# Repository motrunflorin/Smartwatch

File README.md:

Functionalities:

* Wi-Fi and BLE communication via ESP32
* IMU 6-axis BMI085 for motion sensing
* DRV2605L for haptic feedback
* LiPo battery with MCP73831 charging circuit
* USB-C port for programming and charging
* 1.28-inch LCD display, 240x240 pixels for visual output
* Electronics must fit into the provided case

(All datasheets and schematics are in the Components folder)

Constraints:

* No straight angles in traces.
* Power traces must meet the required dimensions.
* Decoupling capacitors (100nF) should be placed as close as possible to the power pins of modules and ICs.
* For double-sided boards, avoid vias in power traces.
* Main components should be placed according to the mechanical dimension and placement document.
* Power traces (VCC, VUSB, VBUS, 3V3, etc.) should have a width of 0.3mm, and data signals at least 0.125mm.
* The ESP32 antenna should be placed toward the PCB edge, with the PCB cutout beneath it.

Notes and Recommendations:

* Use SMD resistors and capacitors in 0402 package, unless specified otherwise (e.g., 0603, tantalum).
* Component placement should be on the TOP layer (except for test pads, SD card socket, LCD connector, and NOR Flash).
* Routing can be on both top and bottom layers. If using two layers, ensure the ground plane is appropriately designed.
* For DRC checks, load the verification file from the provided archive.
* Apply Via Stitching between the two ground planes, especially near the ESP32 module.
* Ignore "Only INPUT pins on NET ID" error.
* Do not route signals under the ESP32 antenna; the area beneath it must be cut out to minimize interference.
* Errors due to button, header, and USB port placement are disregarded.
* Test pads should be placed only on the back of the PCB, clearly marked in silkscreen with signal names.
* Use the provided library ([hector_watch.zip file]) for component symbols and footprints, except for:
    - Buttons ([button.pdf file])
    - LCD connector (draw your own footprints based on the LCD datasheet).

Files:

* Schematics: Schematics.zip file
* DRC check: DRC_check.zip file
* PCB Dimensions & Placement: [dimensions.pdf file]

Additional Notes:

* The recommended PCB dimensions and component placement can be found in the [dimensions.pdf file], with all measurements in mm.
* The placement is just a recommendation to ensure the PCB buttons align with the physical buttons on the case.
* You are free to modify the placement, as long as you also adjust the case.
* Additionally, modify the case to allow access to the SD card and USB-C port if they do not align properly.

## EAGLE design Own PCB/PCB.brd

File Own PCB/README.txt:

for the power traces (3V3), I maintained a width of 0.3 mm, while the rest have 0.127 mm;
!! correction: due to files not being saved properly, I had sync errors between schematics and PCB, and I had to delete the 3V3 traces and modify them with a width of 0.127 mm;

I couldn't group the test pads in a regular shape, and the TX test pad is not in the grouping in order to connect it to the corresponding pin;
(initially, I designed the test pad arrangement as three distinct groups, placed as strategically as possible near the pins they needed to be connected to, in order to have the most optimal traces);

the 100 nF decoupling capacitors were placed as close as possible to the power supply pins;

the main components were placed according to the specifications in the dimensions document, with almost negligible errors, on the order of 10^-3 mm;

the ESP32 module's antenna was placed towards the outer edge of the PCB, and the PCB was cut out as precisely as possible under the antenna;

the test pads, the SD card socket, the LCD connector, and the NOR Flash circuit were placed on the Top layer;

the footprints for the buttons and the LCD display connector were made according to the datasheet;

I tried as much as possible to keep all the component groupings from the schematics together, such as the diode grouping, for example;

I also tried to position the components as close as possible to their corresponding connections from the schematics to the PCB, such as the R1-USB resistor of the USB4110-GF-A module;

ERRORS: resistors R11 and R9 were not connected as I couldn't find a viable trace;

silkscreen was done for the test pads with a width of 0.4 mm.

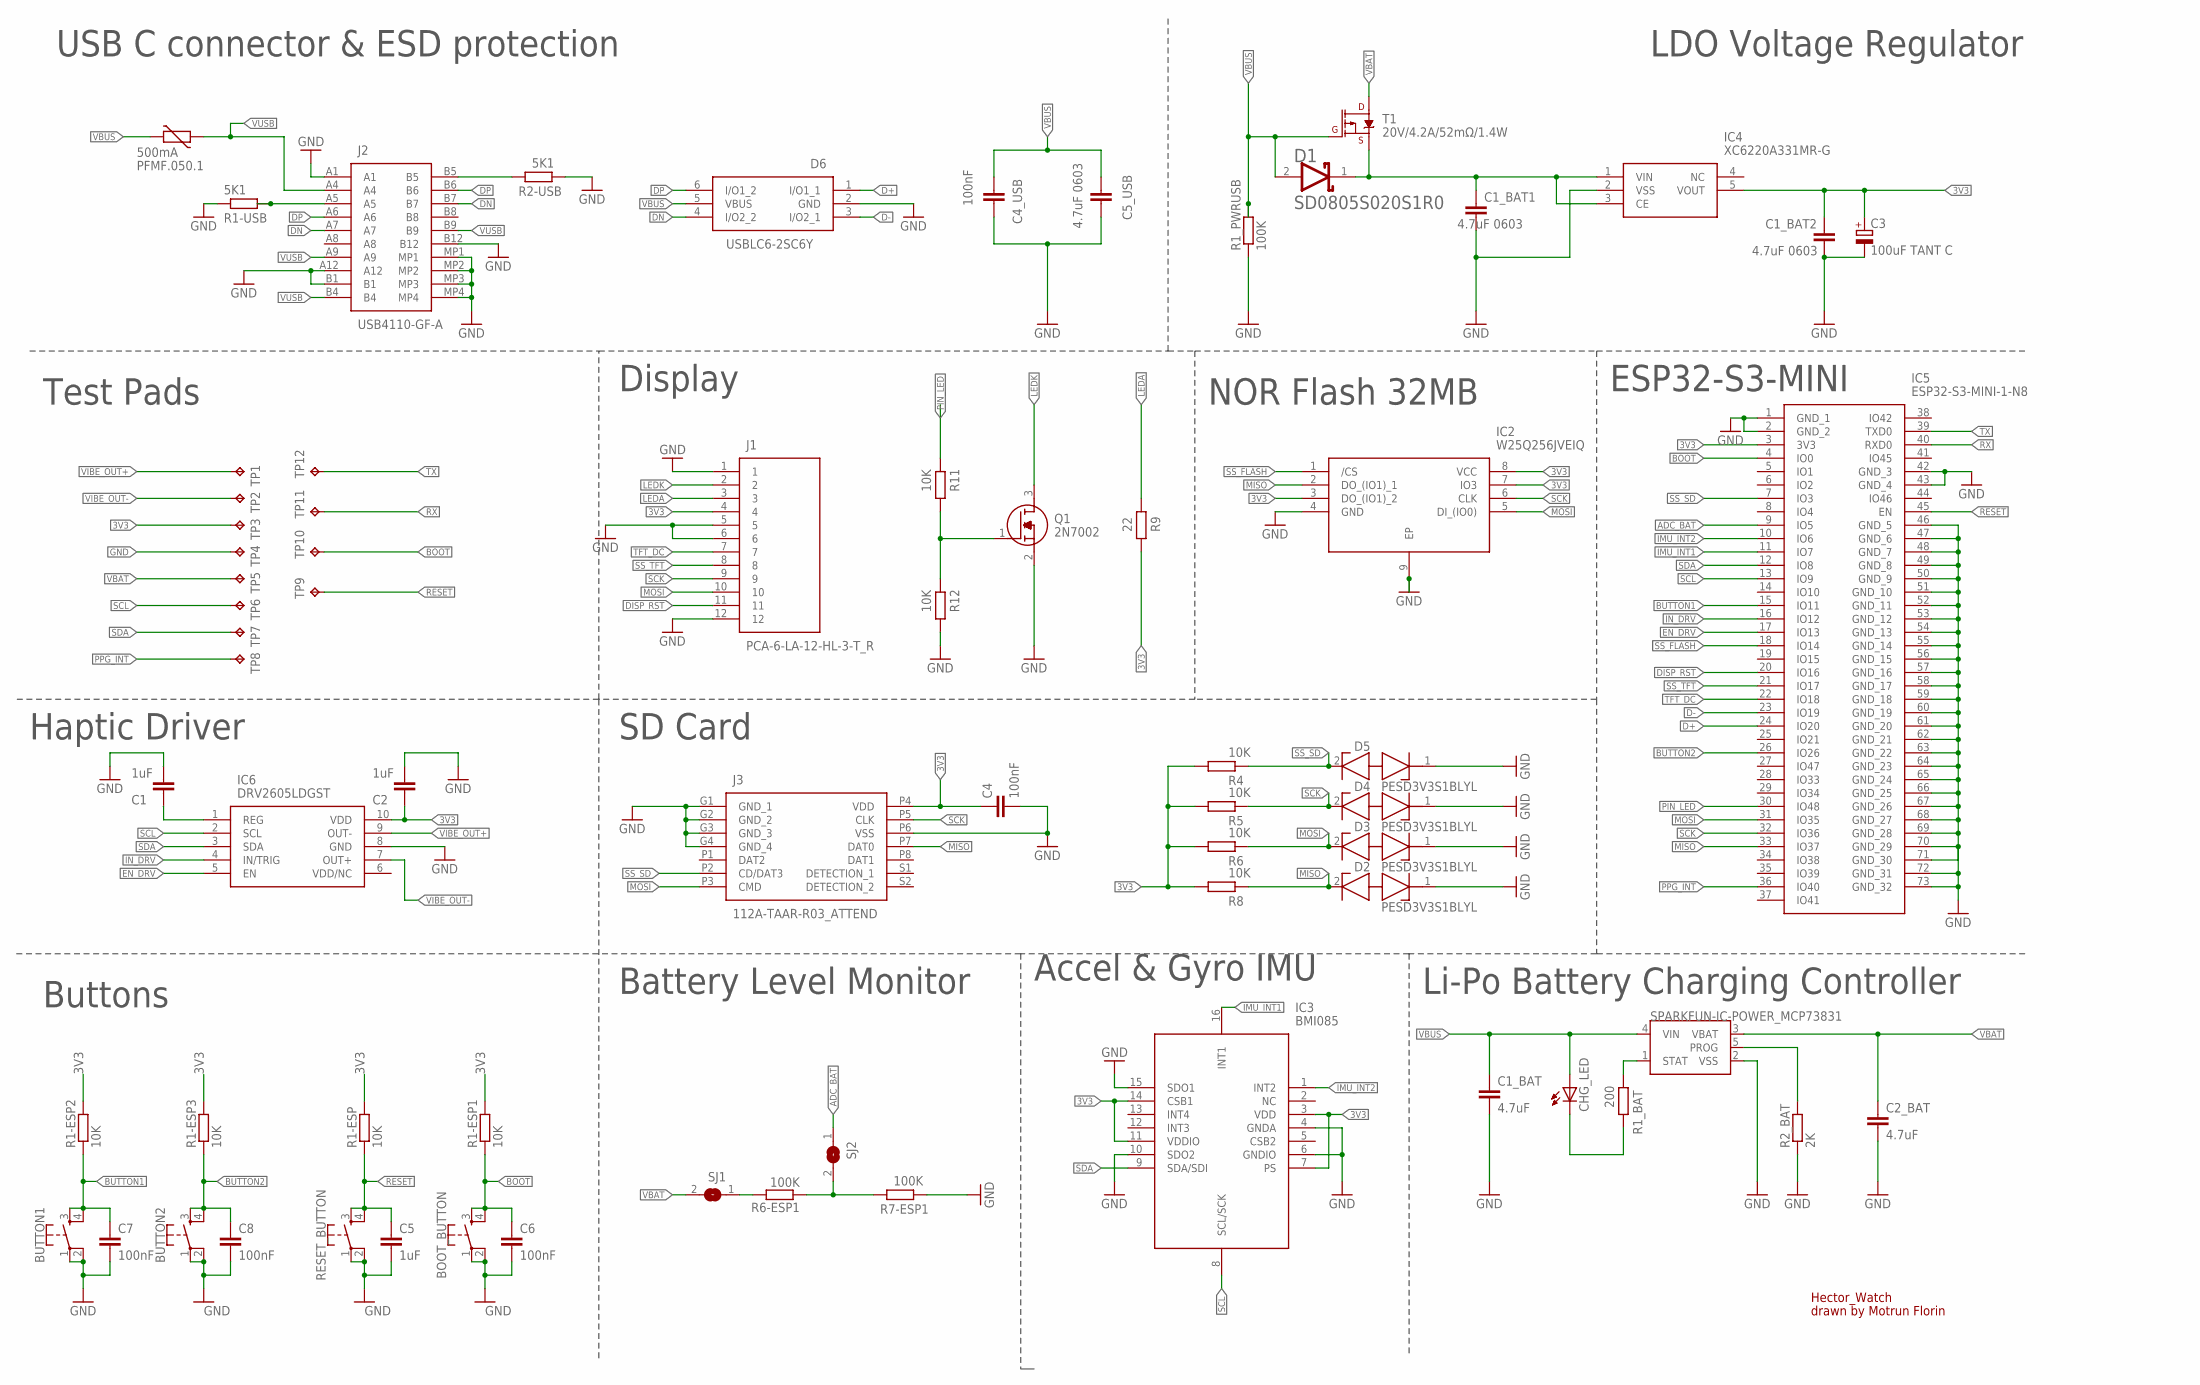
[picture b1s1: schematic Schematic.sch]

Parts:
BOOT_BUTTON: SPARKFUN-SWITCHES_MOMENTARY-SWITCH-SPST-2-SMD-4.6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; SPARKFUN-SWITCHES_TACTILE_SWITCH_SMD_4.6X2.8MM
BUTTON1, BUTTON2: SPARKFUN-SWITCHES_MOMENTARY-SWITCH-SPST-2-SMD-4.6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; SPARKFUN-SWITCHES_TACTILE_SWITCH_SMD_4.6X2.8MM
C1, C2, C5: 1uF; EAGLE-LTSPICE_C0402
C1_BAT, C2_BAT: 4.7uF; EAGLE-LTSPICE_C0402
C1_BAT1, C1_BAT2, C5_USB: 4.7uF 0603; RCL_C0603
C3: 100uF TANT C; CT3528
C4, C4_USB, C6, C7, C8: 100nF; EAGLE-LTSPICE_C0402
CHG_LED: ADAFRUIT_LEDCHIP-LED0603; ADAFRUIT_CHIP-LED0603
D1: AVX---SD0805S020S1R0_AVX_SD0805S020S1R0AVX_SD0805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; AVX---SD0805S020S1R0_AVX_SD0805S020S1R0_0
D2, D3, D4, D5: PESD3V3S1BLYL; PESD5V0S1BL315
D6: USBLC6-2SC6Y; SOT95P280X145-6N
IC2: W25Q256JVEIQ; SON127P800X600X80-9N
IC3: BMI085
IC4: XC6220A331MR-G; SOT95P280X120-5N
IC5: ESP32-S3-MINI-1-N8; ESP32S3MINI1N8
IC6: DRV2605LDGST; SOP50P490X110-10N
J1: PCA-6-LA-12-HL-3-T_R; PCA6LA12HL3TR
J2: USB4110-GF-A; USB4110GFA
J3: 112A-TAAR-R03_ATTEND; 112ATAARR03ATTEND
PFMF.050.1: 500mA; VARISTOR_CT/CN1812
Q1: 2N7002; SOT96P240X120-3N
R1-ESP, R1-ESP1, R1-ESP2, R1-ESP3, R4, R5, R6, R8, R11, R12: 10K; EAGLE-LTSPICE_R0402
R1-USB, R2-USB: 5K1; EAGLE-LTSPICE_R0402
R1_BAT: 200; EAGLE-LTSPICE_R0402
R1_PWRUSB, R6-ESP1, R7-ESP1: 100K; EAGLE-LTSPICE_R0402
R2_BAT: 2K; EAGLE-LTSPICE_R0402
R9: 22; EAGLE-LTSPICE_R0402
RESET_BUTTON: SPARKFUN-SWITCHES_MOMENTARY-SWITCH-SPST-2-SMD-4.6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; SPARKFUN-SWITCHES_TACTILE_SWITCH_SMD_4.6X2.8MM
SJ1, SJ2: SJ
T1: 20V/4.2A/52mΩ/1.4W; SPARKFUN-DISCRETESEMI_SOT23-3
TP1, TP2, TP3, TP4, TP5, TP6, TP7, TP8, TP9, TP10, TP11, TP12: TPTP20R; TP20R
U1: SPARKFUN-IC-POWER_MCP73831; SPARKFUN-IC-POWER_SOT23-5

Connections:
3V3: C1_BAT2.1, C2.2, C3.+, C4.1, IC2.3 (DO_(IO1)_2), IC2.7 (IO3), IC2.8 (VCC), IC3.3 (VDD), IC3.7 (PS), IC3.11 (VDDIO), IC3.14 (CSB1), IC4.5 (VOUT), IC5.3 (3V3), IC6.10 (VDD), J1.4, J3.P4 (VDD), R1-ESP.2, R1-ESP1.2, R1-ESP2.2, R1-ESP3.2, R4.1, R5.1, R6.1, R8.1, R9.1, TP3.TP
ADC_BAT: IC5.9 (IO5), SJ2.1
BOOT: BOOT_BUTTON.3, BOOT_BUTTON.4, C6.1, IC5.4 (IO0), R1-ESP1.1, TP10.TP
BUTTON1: BUTTON1.3, BUTTON1.4, C7.1, IC5.15 (IO11), R1-ESP2.1
BUTTON2: BUTTON2.3, BUTTON2.4, C8.1, IC5.26 (IO26), R1-ESP3.1
D+: D6.1 (I/O1_1), IC5.24 (IO20)
D-: D6.3 (I/O2_1), IC5.23 (IO19)
DISP_RST: IC5.20 (IO16), J1.11
DN: D6.4 (I/O2_2), J2.A7, J2.B7
DP: D6.6 (I/O1_2), J2.A6, J2.B6
EN_DRV: IC5.17 (IO13), IC6.5 (EN)
GND: BOOT_BUTTON.1, BOOT_BUTTON.2, BUTTON1.1, BUTTON1.2, BUTTON2.1, BUTTON2.2, C1.1, C1_BAT.2, C1_BAT1.2, C1_BAT2.2, C2.1, C2_BAT.2, C3.-, C4.2, C4_USB.1, C5.2, C5_USB.2, C6.2, C7.2, C8.2, D2.1 (K1), D3.1 (K1), D4.1 (K1), D5.1 (K1), D6.2 (GND), IC2.4 (GND), IC2.9 (EP), IC3.4 (GNDA), IC3.6 (GNDIO), IC3.10 (SDO2), IC3.15 (SDO1), IC4.2 (VSS), IC5.1 (GND_1), IC5.2 (GND_2), IC5.42 (GND_3), IC5.43 (GND_4), IC5.46 (GND_5), IC5.47 (GND_6), IC5.48 (GND_7), IC5.49 (GND_8), IC5.50 (GND_9), IC5.51 (GND_10), IC5.52 (GND_11), IC5.53 (GND_12), IC5.54 (GND_13), IC5.55 (GND_14), IC5.56 (GND_15), IC5.57 (GND_16), IC5.58 (GND_17), IC5.59 (GND_18), IC5.60 (GND_19), IC5.61 (GND_20), IC5.62 (GND_21), IC5.63 (GND_22), IC5.64 (GND_23), IC5.65 (GND_24), IC5.66 (GND_25), IC5.67 (GND_26), IC5.68 (GND_27), IC5.69 (GND_28), IC5.70 (GND_29), IC5.71 (GND_30), IC5.72 (GND_31), IC5.73 (GND_32), IC6.8 (GND), J1.1, J1.5, J1.6, J1.12, J2.A1, J2.A12, J2.B1, J2.B12, J2.MP1, J2.MP2, J2.MP3, J2.MP4, J3.G1 (GND_1), J3.G2 (GND_2), J3.G3 (GND_3), J3.G4 (GND_4), J3.P6 (VSS), Q1.2 (S), R1-USB.1, R1_PWRUSB.1, R2-USB.2, R2_BAT.1, R7-ESP1.2, R12.1, RESET_BUTTON.1, RESET_BUTTON.2, TP4.TP, U1.2 (VSS)
IMU_INT1: IC3.16 (INT1), IC5.11 (IO7)
IMU_INT2: IC3.1 (INT2), IC5.10 (IO6)
IN_DRV: IC5.16 (IO12), IC6.4 (IN/TRIG)
LEDA: J1.3, R9.2
LEDK: J1.2, Q1.3 (D)
MISO: D2.2 (K2), IC2.2 (DO_(IO1)_1), IC5.33 (IO37), J3.P7 (DAT0), R8.2
MOSI: D3.2 (K2), IC2.5 (DI_(IO0)), IC5.31 (IO35), J1.10, J3.P3 (CMD), R6.2
unnamed: J2.B5, R2-USB.1
unnamed: J2.A5, R1-USB.2
unnamed: C1.2, IC6.1 (REG)
unnamed: C1_BAT1.1, D1.1 (CATHODE), IC4.1 (VIN), IC4.3 (CE), T1.2 (S)
unnamed: CHG_LED.C, R1_BAT.1
unnamed: R6-ESP1.2, SJ1.1
unnamed: R6-ESP1.1, R7-ESP1.1, SJ2.2
unnamed: R2_BAT.2, U1.5 (PROG)
unnamed: Q1.1 (G), R11.1, R12.2
unnamed: R1_BAT.2, U1.1 (STAT)
PIN_LED: IC5.30 (IO48), R11.2
PPG_INT: IC5.36 (IO40), TP8.TP
RESET: C5.1, IC5.45 (EN), R1-ESP.1, RESET_BUTTON.3, RESET_BUTTON.4, TP9.TP
RX: IC5.40 (RXD0), TP11.TP
SCK: D4.2 (K2), IC2.6 (CLK), IC5.32 (IO36), J1.9, J3.P5 (CLK), R5.2
SCL: IC3.8 (SCL/SCK), IC5.13 (IO9), IC6.2 (SCL), TP6.TP
SDA: IC3.9 (SDA/SDI), IC5.12 (IO8), IC6.3 (SDA), TP7.TP
SS_FLASH: IC2.1 (/CS), IC5.18 (IO14)
SS_SD: D5.2 (K2), IC5.7 (IO3), J3.P2 (CD/DAT3), R4.2
SS_TFT: IC5.21 (IO17), J1.8
TFT_DC: IC5.22 (IO18), J1.7
TX: IC5.39 (TXD0), TP12.TP
VBAT: C2_BAT.1, SJ1.2, T1.3 (D), TP5.TP, U1.3 (VBAT)
VBUS: C1_BAT.1, C4_USB.2, C5_USB.1, CHG_LED.A, D1.2 (ANODE), D6.5 (VBUS), PFMF.050.1.2, R1_PWRUSB.2, T1.1 (G), U1.4 (VIN)
VIBE_OUT+: IC6.9 (OUT-), TP1.TP
VIBE_OUT-: IC6.7 (OUT+), TP2.TP
VUSB: J2.A4, J2.A9, J2.B4, J2.B9, PFMF.050.1.1

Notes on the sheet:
USB C connector & ESD protection
LDO Voltage Regulator
ESP32-S3-MINI
NOR Flash 32MB
Display
Test Pads
Haptic Driver
SD Card
Li-Po Battery Charging Controller
Accel & Gyro IMU
Battery Level Monitor
Buttons
Hector_Watch
drawn by Motrun Florin

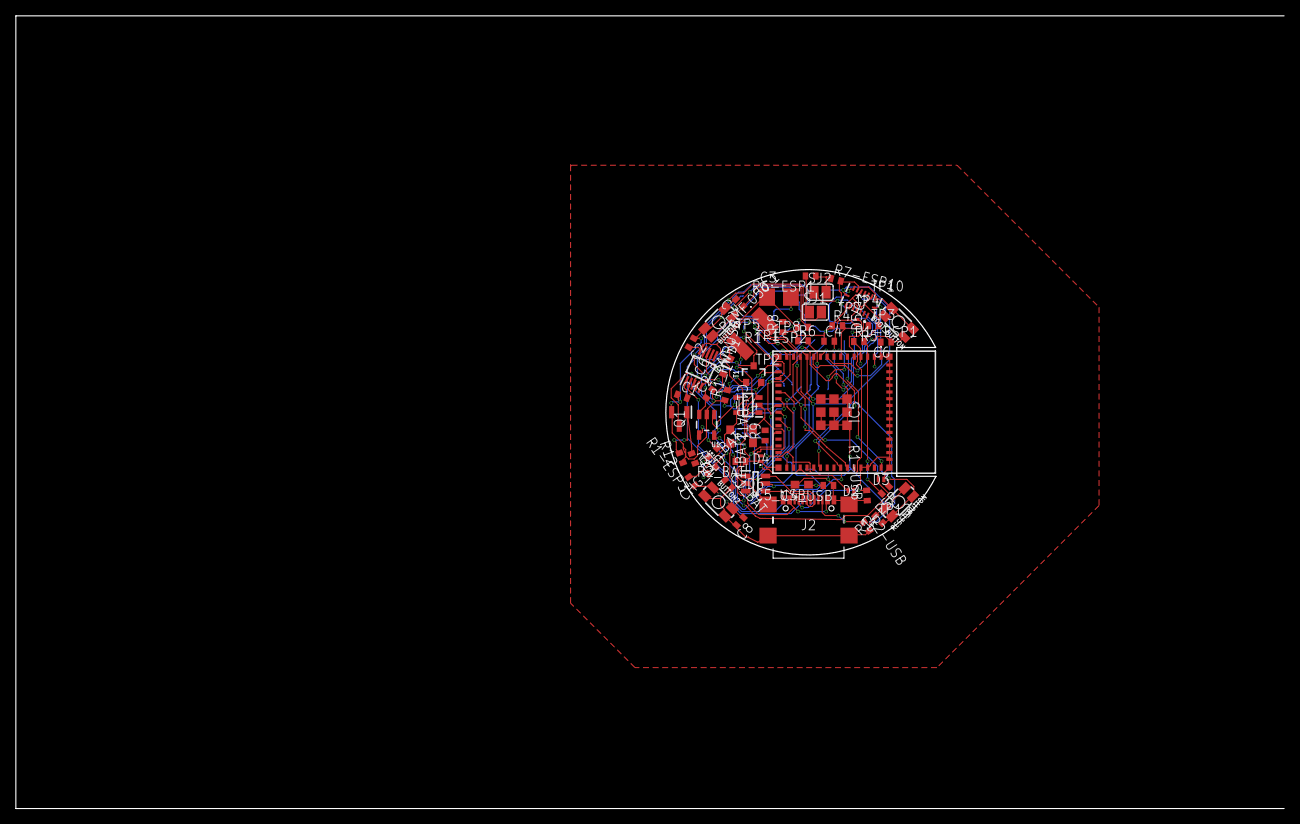
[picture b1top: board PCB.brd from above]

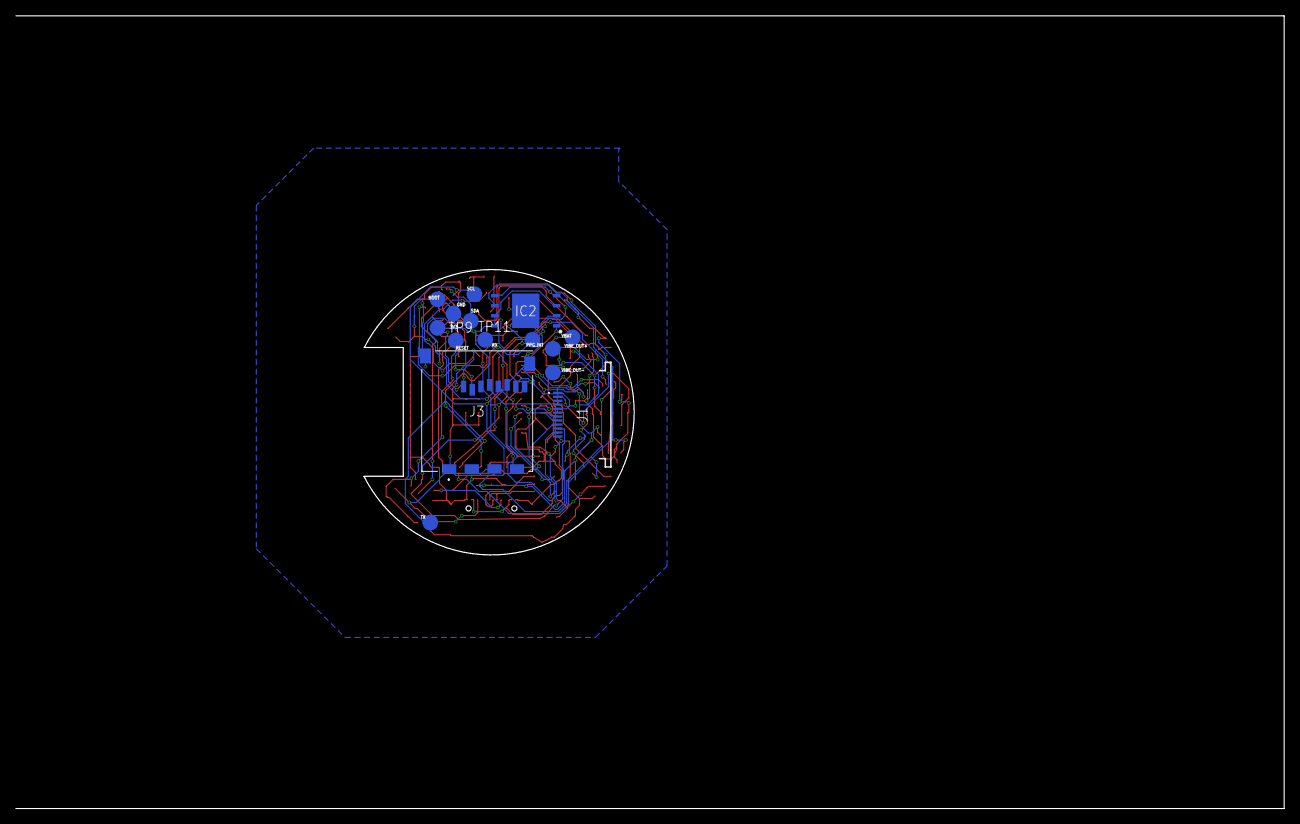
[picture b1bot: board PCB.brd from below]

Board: 2 copper layers, 160.0 x 100.0 mm, 69 parts (15 on the bottom side), 46 nets.
